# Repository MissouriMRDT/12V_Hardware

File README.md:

# 12V_Hardware
12V Distribution Board

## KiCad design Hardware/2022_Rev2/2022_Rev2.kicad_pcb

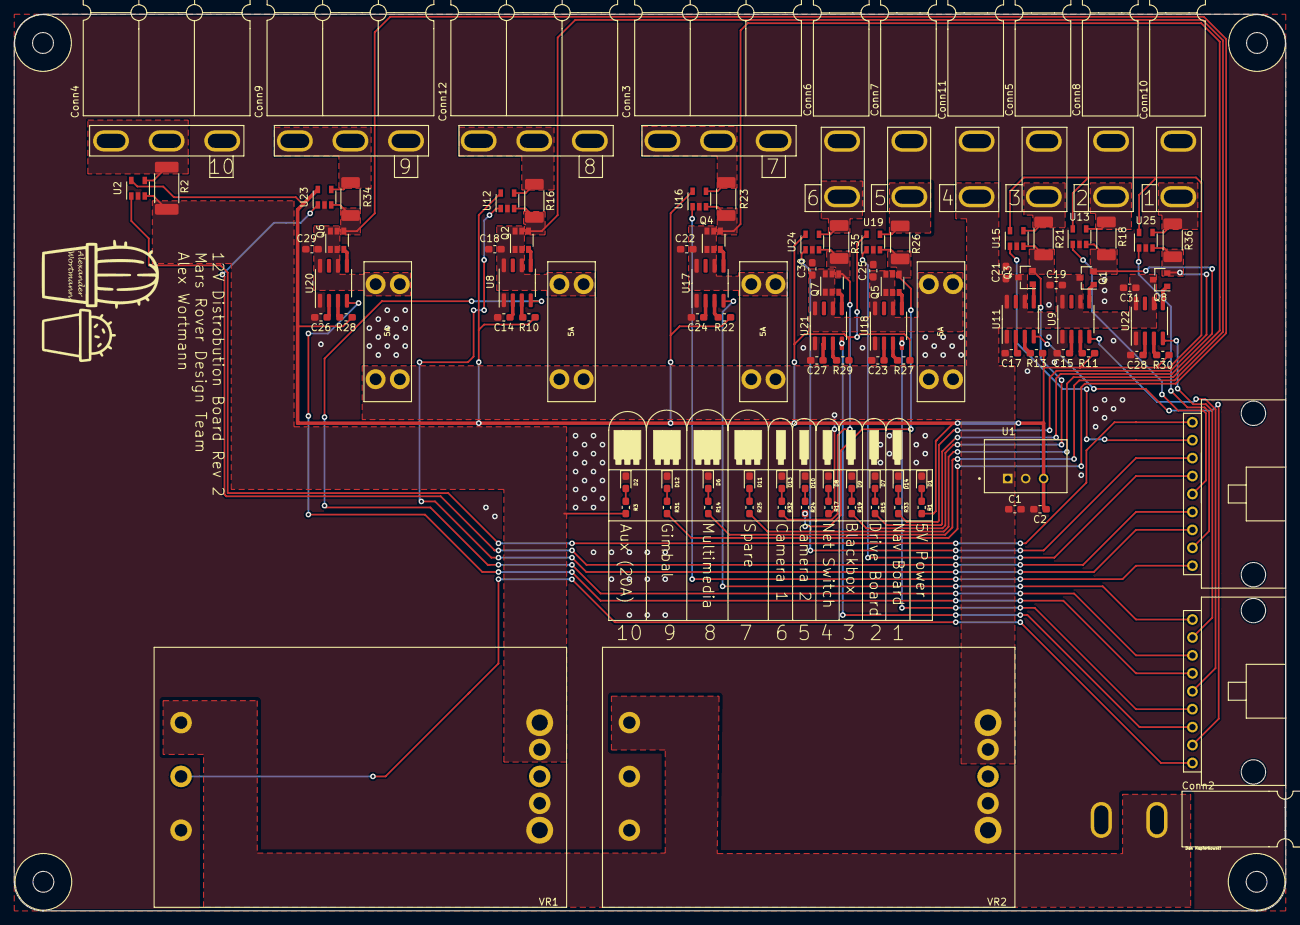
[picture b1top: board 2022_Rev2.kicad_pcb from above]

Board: 2 copper layers, 180.1 x 127.0 mm, 102 parts (0 on the bottom side), 79 nets.

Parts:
C1, C18, C19, C21, C22, C25, C29, C30, C31: 10uF; C_0603_1608Metric_Pad1.05x0.95mm_HandSolder
C2: 22uF; C_0603_1608Metric_Pad1.05x0.95mm_HandSolder
C14, C15, C17, C23, C24, C26, C27, C28: 0.1uF; C_0603_1608Metric_Pad1.05x0.95mm_HandSolder
Conn1, Conn13: Molex_SL_09; MOLEX_SL_09_Horizontal
Conn2: Pack; Square_Anderson_2_H_Stacked
Conn3: Spare; Square_Anderson_3_H_Side_By_Side
Conn4: Aux; Square_Anderson_3_H_Side_By_Side
Conn5: BBB; Square_Anderson_2_H_Stacked_PV
Conn6: Cam1; Square_Anderson_2_H_Stacked_PV
Conn7: Cam2; Square_Anderson_2_H_Stacked_PV
Conn8: Drive; Square_Anderson_2_H_Stacked_PV
Conn9: Gimbal; Square_Anderson_3_H_Side_By_Side
Conn10: Nav; Square_Anderson_2_H_Stacked_PV
Conn11: Network Switch; Square_Anderson_2_H_Stacked_PV
Conn12: Multimedia; Square_Anderson_3_H_Side_By_Side
D1, D2, D6, D7, D8, D9, D10, D11, D12, D13, D14: LED; D_0603_1608Metric_Pad1.05x0.95mm_HandSolder
F1, F6, F8, F9: 5A; ATC_Fuse_Block
Q1, Q3, Q8: IRLML2803TRPBF; SOT-23
Q2, Q4, Q5, Q6, Q7: FDC855N; SuperSOT-6
R1: 330; R_0603_1608Metric_Pad1.05x0.95mm_HandSolder
R2: 0.0015; R_2512_6332Metric_Pad1.52x3.35mm_HandSolder
R3, R14, R15, R17, R19, R24, R25, R31, R32, R33: 1k; R_0603_1608Metric_Pad1.05x0.95mm_HandSolder
R10, R11, R13, R22, R27, R28, R29, R30: 5.1k; R_0603_1608Metric_Pad1.05x0.95mm_HandSolder
R16, R18, R21, R23, R26, R34, R35, R36: 0.003; R_2010_5025Metric_Pad1.52x2.65mm_HandSolder
U1: TSR1-2433; TSR_1-2433
U2, U12, U13, U15, U16, U19, U23, U24, U25: INA281; SOT-23-5
U8, U9, U11, U17, U18, U20, U21, U22: LT1910; SOIC-8_3.9x4.9mm_P1.27mm
VR1, VR2: Q36SR12020NRFA

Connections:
+5V: C2.1, R1.2, R10.1, R11.1, R13.1, R22.1, R27.1, R28.1, R29.1, R30.1, U1.3, U2.5, U12.5, U13.5, U15.5, U16.5, U19.5, U23.5, U24.5, U25.5
+12VA: C1.1, C19.1, C21.1, C31.1, Conn11.2, F1.1, F6.1, F8.1, F9.1, Q1.3, Q3.3, Q8.3, R17.2, U1.1, U9.6, U9.8, U11.6, U11.8, U22.6, U22.8, VR2.7, VR2.8
+36V: Conn2.4, VR1.1, VR2.1
/12V/Anderson_BBB: Conn5.2, R21.2, U15.4
/12V/Anderson_Cam1: Conn6.2, R35.2, U24.4
/12V/Anderson_Cam2: Conn7.2, R26.2, U19.4
/12V/Anderson_Drive: Conn8.2, R18.2, U13.4
/12V/Anderson_GimAct: Conn9.2, Conn9.3, R34.2, U23.4
/12V/Anderson_MultiAct: Conn12.2, Conn12.3, R16.2, U12.4
/12V/Anderson_Nav: Conn10.2, R36.2, U25.4
/12V/Anderson_Spare: Conn3.2, Conn3.3, R23.2, U16.4
Current_Sense_Aux: Conn1.1, U2.1
Current_Sense_BBB: Conn1.2, U15.1
Current_Sense_Cam1: Conn1.3, U24.1
Current_Sense_Cam2: Conn1.4, U19.1
Current_Sense_Drive: Conn1.5, U13.1
Current_Sense_Gim: Conn1.6, U23.1
Current_Sense_Multi: Conn1.7, U12.1
Current_Sense_Nav: Conn1.8, U25.1
Current_Sense_Spare: Conn1.9, U16.1
Driver_Aux: Conn13.9, VR1.2
Driver_BBB: Conn13.8, U11.4
Driver_Cam1: Conn13.7, U21.4
Driver_Cam2: Conn13.6, U18.4
Driver_Drive: Conn13.5, U9.4
Driver_Gim: Conn13.4, U20.4
Driver_Multi: Conn13.3, U8.4
Driver_Nav: Conn13.2, U22.4
Driver_Spare: Conn13.1, U17.4
GND: C1.2, C2.2, C14.2, C15.2, C17.2, C18.2, C19.2, C21.2, C22.2, C23.2, C24.2, C25.2, C26.2, C27.2, C28.2, C29.2, C30.2, C31.2, Conn2.1, Conn3.1, Conn4.1, Conn5.1, Conn6.1, Conn7.1, Conn8.1, Conn9.1, Conn10.1, Conn11.1, Conn12.1, D1.1, D2.1, D6.1, D7.1, D8.1, D9.1, D10.1, D11.1, D12.1, D13.1, D14.1, U1.2, U2.2, U8.1, U9.1, U11.1, U12.2, U13.2, U15.2, U16.2, U17.1, U18.1, U19.2, U20.1, U21.1, U22.1, U23.2, U24.2, U25.2, VR1.3, VR1.4, VR1.5, VR2.2, VR2.3, VR2.4, VR2.5
unnamed: C14.1, U8.2
unnamed: C15.1, U9.2
unnamed: C17.1, U11.2
unnamed: C18.1, F6.2, Q2.1, Q2.2, Q2.5, Q2.6, U8.6, U8.8
unnamed: C22.1, F1.2, Q4.1, Q4.2, Q4.5, Q4.6, U17.6, U17.8
unnamed: C23.1, U18.2
unnamed: C24.1, U17.2
unnamed: C25.1, C30.1, F8.2, Q5.1, Q5.2, Q5.5, Q5.6, Q7.1, Q7.2, Q7.5, Q7.6, U18.6, U18.8, U21.6, U21.8
unnamed: C26.1, U20.2
unnamed: C27.1, U21.2
unnamed: C28.1, U22.2
unnamed: C29.1, F9.2, Q6.1, Q6.2, Q6.5, Q6.6, U20.6, U20.8
unnamed: Conn4.2, Conn4.3, R2.2, U2.4
unnamed: D1.2, R1.1
unnamed: D2.2, R3.1
unnamed: D6.2, R14.1
unnamed: D7.2, R15.1
unnamed: D8.2, R17.1
unnamed: D9.2, R19.1
unnamed: D10.2, R24.1
unnamed: D11.2, R25.1
unnamed: D12.2, R31.1
unnamed: D13.2, R32.1
unnamed: D14.2, R33.1
unnamed: Q1.1, U9.5
unnamed: Q1.2, R15.2, R18.1, U13.3
unnamed: Q2.3, U8.5
unnamed: Q2.4, R14.2, R16.1, U12.3
unnamed: Q3.1, U11.5
unnamed: Q3.2, R19.2, R21.1, U15.3
unnamed: Q4.3, U17.5
unnamed: Q4.4, R23.1, R25.2, U16.3
unnamed: Q5.3, U18.5
unnamed: Q5.4, R24.2, R26.1, U19.3
unnamed: Q6.3, U20.5
unnamed: Q6.4, R31.2, R34.1, U23.3
unnamed: Q7.3, U21.5
unnamed: Q7.4, R32.2, R35.1, U24.3
unnamed: Q8.1, U22.5
unnamed: Q8.2, R33.2, R36.1, U25.3
unnamed: R2.1, R3.2, U2.3, VR1.7, VR1.8
unnamed: R10.2, U8.3
unnamed: R11.2, U9.3
unnamed: R13.2, U11.3
unnamed: R22.2, U17.3
unnamed: R27.2, U18.3
unnamed: R28.2, U20.3
unnamed: R29.2, U21.3
unnamed: R30.2, U22.3

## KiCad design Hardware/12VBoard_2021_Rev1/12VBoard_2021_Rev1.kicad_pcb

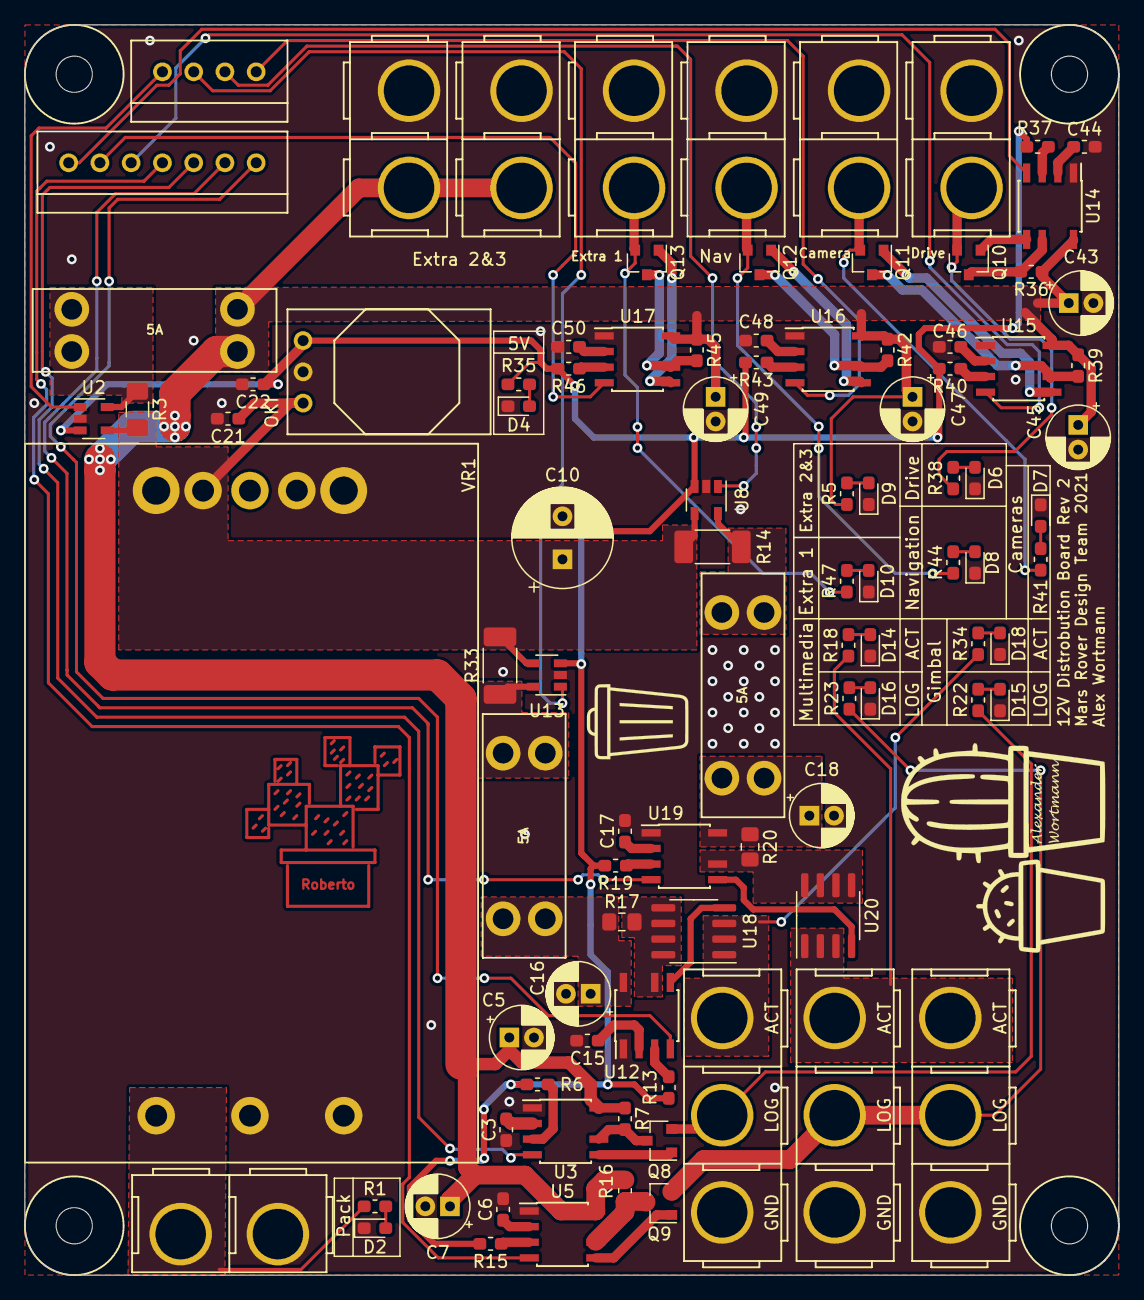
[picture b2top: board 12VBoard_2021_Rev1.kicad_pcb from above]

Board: 2 copper layers, 88.9 x 101.6 mm, 96 parts (0 on the bottom side), 72 nets.

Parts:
C3, C6, C15, C17, C44, C46, C48, C50: 0.1uF; C_0603_1608Metric_Pad1.05x0.95mm_HandSolder
C5, C7, C16, C18, C43, C45, C47, C49: 10uF; CP_Radial_D5.0mm_P2.00mm
C10: 330uF; CP_Radial_D8.0mm_P3.50mm
C21, C22: 10uF; C_0603_1608Metric_Pad1.05x0.95mm_HandSolder
Camera: Camera; Anderson_2_Vertical_Sidy_by_Side
Conn1: Molex_SL_10; MOLEX_SL_07_Vertical
Conn2: Molex_SL_05; MOLEX_SL_04_Vertical
Conn9: Gimbal; Anderson_3_Vertical_Side_by_Side
Conn11: Multimedia; Anderson_3_Vertical_Side_by_Side
Conn12: Extra; Anderson_3_Vertical_Side_by_Side
D2, D4, D6, D7, D8, D9, D10, D14, D15, D16, D18: LED; D_0603_1608Metric_Pad1.05x0.95mm_HandSolder
Drive: Drive; Anderson_2_Vertical_Sidy_by_Side
Extra 1: ExtraL1; Anderson_2_Vertical_Sidy_by_Side
Extra 2&3: ExtraL2; Anderson_2_Vertical_Sidy_by_Side
Extra 2&3#2: ExtraL3; Anderson_2_Vertical_Sidy_by_Side
F1, F2, F3: 5A; ATC_Fuse_Block
Nav: NavBoard; Anderson_2_Vertical_Sidy_by_Side
Pack: PackVoltage; Anderson_2_Vertical_Sidy_by_Side
Q8, Q9, Q10, Q11, Q12, Q13: IRLML2060; SOT-23
R1: 3.3k; R_0603_1608Metric_Pad1.05x0.95mm_HandSolder
R3: 20m; R_1206_3216Metric_Pad1.42x1.75mm_HandSolder
R5, R18, R22, R23, R34, R38, R41, R44, R47: 1.2k; R_0603_1608Metric_Pad1.05x0.95mm_HandSolder
R6, R13, R15, R19, R37, R40, R43, R46: 5.1K; R_0603_1608Metric_Pad1.05x0.95mm_HandSolder
R7, R16, R36, R39, R42, R45: 0.01; R_0603_1608Metric_Pad1.05x0.95mm_HandSolder
R14, R33: 20m; R_2010_5025Metric_Pad1.52x2.65mm_HandSolder
R17, R20: 0.01; R_0805_2012Metric_Pad1.15x1.40mm_HandSolder
R35: 510; R_0603_1608Metric_Pad1.05x0.95mm_HandSolder
U2, U8, U13: INA198; SOT-23-5
U3, U5, U12, U14, U15, U16, U17, U19: LT1910; SOIC-8-N7_3.9x4.9mm_P1.27mm
U9: OKI; OKI_Horizontal
U18, U20: FDS66900AS; SOIC-8_3.9x4.9mm_P1.27mm
VR1: Q36SR12020NRFA

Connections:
+5V: C22.1, R6.2, R13.2, R15.2, R19.2, R35.2, R37.2, R40.2, R43.2, R46.2, U2.3, U8.3, U9.3, U13.3
/High Current Outputs/12VActuation: C10.1, C21.1, R3.2, R14.2, R33.2, U2.4, U8.4, U9.1, U13.4, VR1.7, VR1.8
/High Current Outputs/12VLogic: C5.1, C7.1, C43.1, C45.1, C47.1, C49.1, Extra 2&3.2, Extra 2&3#2.2, F2.2, R5.1, R7.1, R16.1, R36.1, R39.1, R42.1, R45.1, U3.8, U5.8, U14.8, U15.8, U16.8, U17.8
/High Current Outputs/Gimbal/12V5AGimbal: Conn9.3, R34.1, U18.1, U18.2, U18.3
/High Current Outputs/Gimbal/12V5AON: C16.1, F3.1, R17.1, U12.8
/High Current Outputs/Gimbal/12VLogicGimbal: Conn9.2, Q8.2, R22.1
/High Current Outputs/GimbalCTL_Act: Conn1.1, U12.4
/High Current Outputs/GimbalCTL_Log: Conn1.3, U3.4
/High Current Outputs/GimbalSense: Conn2.3, U13.1
/High Current Outputs/MultiMediaCTL_Log: Conn1.4, U5.4
/High Current Outputs/Multimedia/Extra/12V5AMultiMedia: Conn11.3, Conn12.3, R18.1, U20.1, U20.2, U20.3
/High Current Outputs/Multimedia/Extra/12V5AON: C18.1, F1.1, R20.1, U19.8
/High Current Outputs/Multimedia/Extra/12VLogicMultiMedia: Conn11.2, Conn12.2, Q9.2, R23.1
/High Current Outputs/MultimediaCTL_Act: Conn1.2, U19.4
/High Current Outputs/MultimediaSense: Conn2.2, U8.1
/High Current Outputs/PackVoltage: Pack.2, R1.1, VR1.1
/Low Current Outputs/CameraCTL: Conn1.5, U15.4
/Low Current Outputs/CurrentSense: Conn2.4, U2.1
/Low Current Outputs/DriveCTL: Conn1.7, U14.4
/Low Current Outputs/ExtraCTL: Conn1.6, U17.4
/Tiva In/Outputs/NavBoardCTL: Conn2.1, U16.4
GND: C3.2, C5.2, C6.2, C7.2, C10.2, C15.2, C16.2, C17.2, C18.2, C21.2, C22.2, C43.2, C44.2, C45.2, C46.2, C47.2, C48.2, C49.2, C50.2, Camera.1, Conn9.1, Conn11.1, Conn12.1, D2.1, D4.1, D6.1, D7.1, D8.1, D9.1, D10.1, D14.1, D15.1, D16.1, D18.1, Drive.1, Extra 1.1, Extra 2&3.1, Extra 2&3#2.1, Nav.1, Pack.1, U2.2, U3.1, U5.1, U8.2, U9.2, U12.1, U13.2, U14.1, U15.1, U16.1, U17.1, U19.1, VR1.2, VR1.3, VR1.4, VR1.5
unnamed: C3.1, U3.2
unnamed: C6.1, U5.2
unnamed: C15.1, U12.2
unnamed: C17.1, U19.2
unnamed: C44.1, U14.2
unnamed: C46.1, U15.2
unnamed: C48.1, U16.2
unnamed: C50.1, U17.2
unnamed: Camera.2, Q11.2, R41.1
unnamed: Nav.2, Q12.2, R44.1
unnamed: Extra 1.2, Q13.2, R47.1
unnamed: Drive.2, Q10.2, R38.1
unnamed: D2.2, R1.2
unnamed: D4.2, R35.1
unnamed: D6.2, R38.2
unnamed: D7.2, R41.2
unnamed: D8.2, R44.2
unnamed: D9.2, R5.2
unnamed: D10.2, R47.2
unnamed: D14.2, R18.2
unnamed: D15.2, R22.2
unnamed: D16.2, R23.2
unnamed: D18.2, R34.2
unnamed: F1.2, R14.1, U8.5
unnamed: F2.1, R3.1, U2.5
unnamed: F3.2, R33.1, U13.5
unnamed: Q8.1, U3.5
unnamed: Q8.3, R7.2, U3.6
unnamed: Q9.1, U5.5
unnamed: Q9.3, R16.2, U5.6
unnamed: Q10.1, U14.5
unnamed: Q10.3, R36.2, U14.6
unnamed: Q11.1, U15.5
unnamed: Q11.3, R39.2, U15.6
unnamed: Q12.1, U16.5
unnamed: Q12.3, R42.2, U16.6
unnamed: Q13.1, U17.5
unnamed: Q13.3, R45.2, U17.6
unnamed: R6.1, U3.3
unnamed: R13.1, U12.3
unnamed: R15.1, U5.3
unnamed: R17.2, U12.6, U18.5, U18.6, U18.7, U18.8
unnamed: R19.1, U19.3
unnamed: R20.2, U19.6, U20.5, U20.6, U20.7, U20.8
unnamed: R37.1, U14.3
unnamed: R40.1, U15.3
unnamed: R43.1, U16.3
unnamed: R46.1, U17.3
unnamed: U12.5, U18.4
unnamed: U19.5, U20.4

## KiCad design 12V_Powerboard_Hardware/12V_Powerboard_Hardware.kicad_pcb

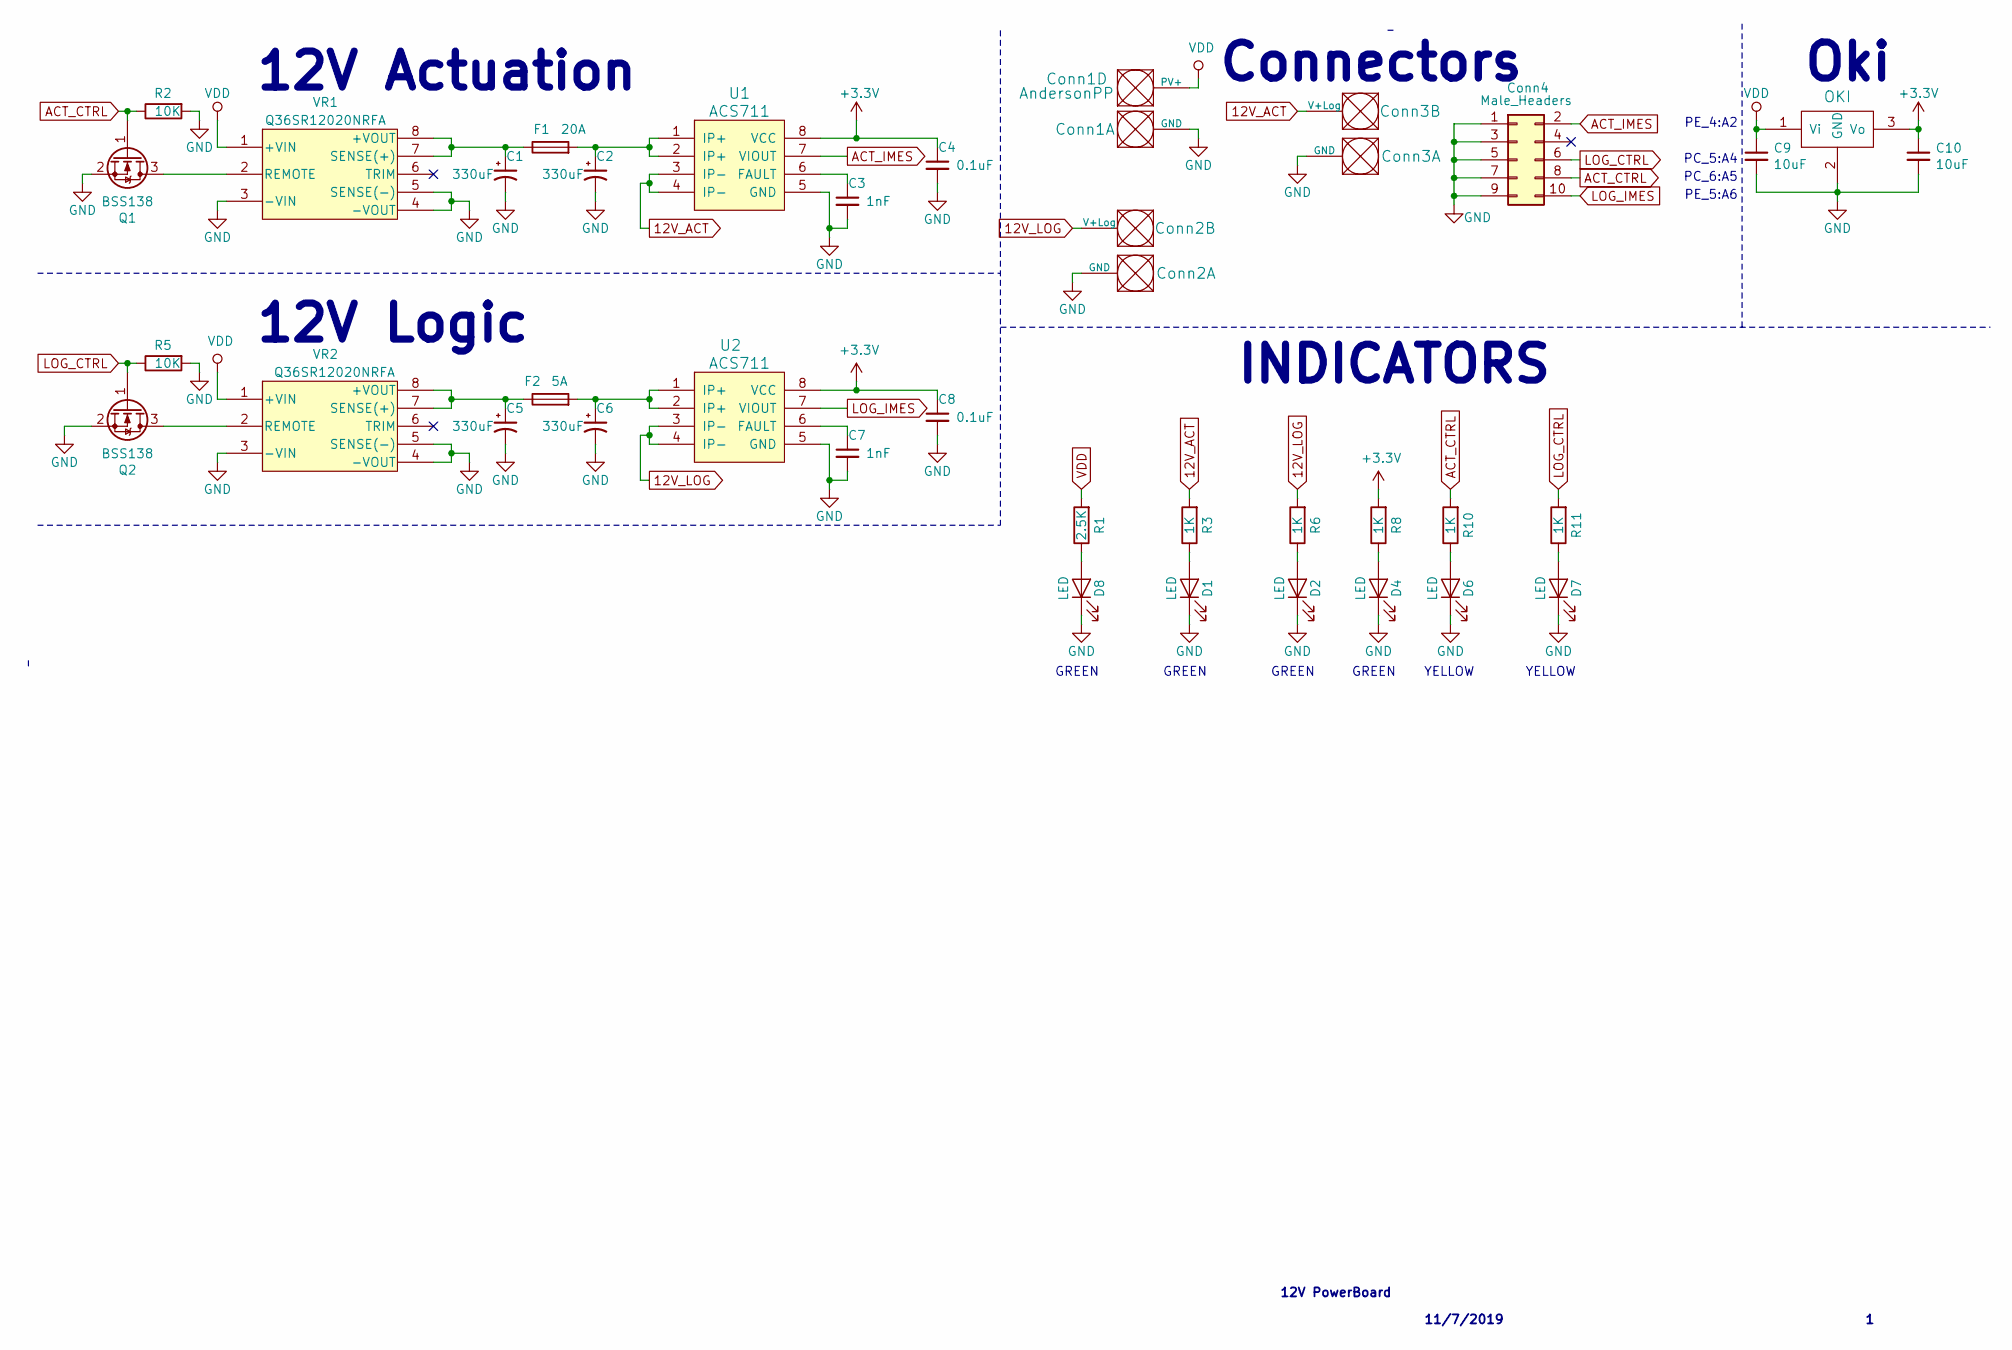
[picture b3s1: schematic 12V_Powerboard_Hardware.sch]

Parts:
C1, C2, C5, C6: 330uF; CP_Radial_D8.0mm_P3.50mm
C3, C7: 1nF; C_0603_1608Metric_Pad1.05x0.95mm_HandSolder
C4, C8: 0.1uF; C_0603_1608Metric_Pad1.05x0.95mm_HandSolder
C9, C10: 10uF; C_0603_1608Metric_Pad1.05x0.95mm_HandSolder
Conn1: AndersonPP; Anderson_2_Horizontal_Stacked
Conn2, Conn3: AndersonPP; Anderson_2_Vertical_Sidy_by_Side
Conn4: Male_Headers; JTAG_ARM_Connector_10_Pin
D1, D2, D4, D6, D7, D8: LED; LED_0603_1608Metric_Pad1.05x0.95mm_HandSolder
F1: 20A; ATC_Fuse_Block
F2: 5A; ATC_Fuse_Block
Q1, Q2: BSS138; SOT-323_SC-70_Handsoldering
R1: 2.5K; R_0603_1608Metric_Pad1.05x0.95mm_HandSolder
R2, R5: 10K; R_0603_1608Metric_Pad1.05x0.95mm_HandSolder
R3, R6, R8, R10, R11: 1K; R_0603_1608Metric_Pad1.05x0.95mm_HandSolder
U1, U2: ACS711; SOIC-8_3.9x4.9mm_P1.27mm
U5: OKI; OKI_Horizontal
VR1, VR2: Q36SR12020NRFA

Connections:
12V_ACT: Conn3.2 (V+Log), R3.2, U1.3 (IP-), U1.4 (IP-)
12V_LOG: Conn2.2 (V+Log), R6.2, U2.3 (IP-), U2.4 (IP-)
+3V3: C4.1, C8.1, C10.1, R8.2, U1.8 (VCC), U2.8 (VCC), U5.3 (Vo)
ACT_CTRL: Conn4.8, Q1.1 (G), R2.1, R10.2
ACT_IMES: Conn4.2, U1.7 (VIOUT)
GND: C1.2, C2.2, C3.2, C4.2, C5.2, C6.2, C7.2, C8.2, C9.2, C10.2, Conn1.1 (GND), Conn2.1 (GND), Conn3.1 (GND), Conn4.1, Conn4.3, Conn4.5, Conn4.7, Conn4.9, D1.1 (K), D2.1 (K), D4.1 (K), D6.1 (K), D7.1 (K), D8.1 (K), Q1.2 (S), Q2.2 (S), R2.2, R5.2, U1.5 (GND), U2.5 (GND), U5.2 (GND), VR1.3 (-VIN), VR1.4 (-VOUT), VR1.5 (SENSE(-)), VR2.3 (-VIN), VR2.4 (-VOUT), VR2.5 (SENSE(-))
LOG_CTRL: Conn4.6, Q2.1 (G), R5.1, R11.2
LOG_IMES: Conn4.10, U2.7 (VIOUT)
unnamed: C1.1, F1.1, VR1.7 (SENSE(+)), VR1.8 (+VOUT)
unnamed: C2.1, F1.2, U1.1 (IP+), U1.2 (IP+)
unnamed: C3.1, U1.6 (FAULT)
unnamed: C5.1, F2.1, VR2.7 (SENSE(+)), VR2.8 (+VOUT)
unnamed: C6.1, F2.2, U2.1 (IP+), U2.2 (IP+)
unnamed: C7.1, U2.6 (FAULT)
unnamed: D1.2 (A), R3.1
unnamed: D2.2 (A), R6.1
unnamed: D4.2 (A), R8.1
unnamed: D6.2 (A), R10.1
unnamed: D7.2 (A), R11.1
unnamed: D8.2 (A), R1.1
unnamed: Q1.3 (D), VR1.2 (REMOTE)
unnamed: Q2.3 (D), VR2.2 (REMOTE)
VDD: C9.1, Conn1.4 (PV+), R1.2, U5.1 (Vi), VR1.1 (+VIN), VR2.1 (+VIN)

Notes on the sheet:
12V Logic
12V PowerBoard
11/7/2019
12V Actuation
Oki
PE_4:A2
PE_5:A6
PC_6:A5
PC_5:A4
Connectors
GREEN
YELLOW
INDICATORS

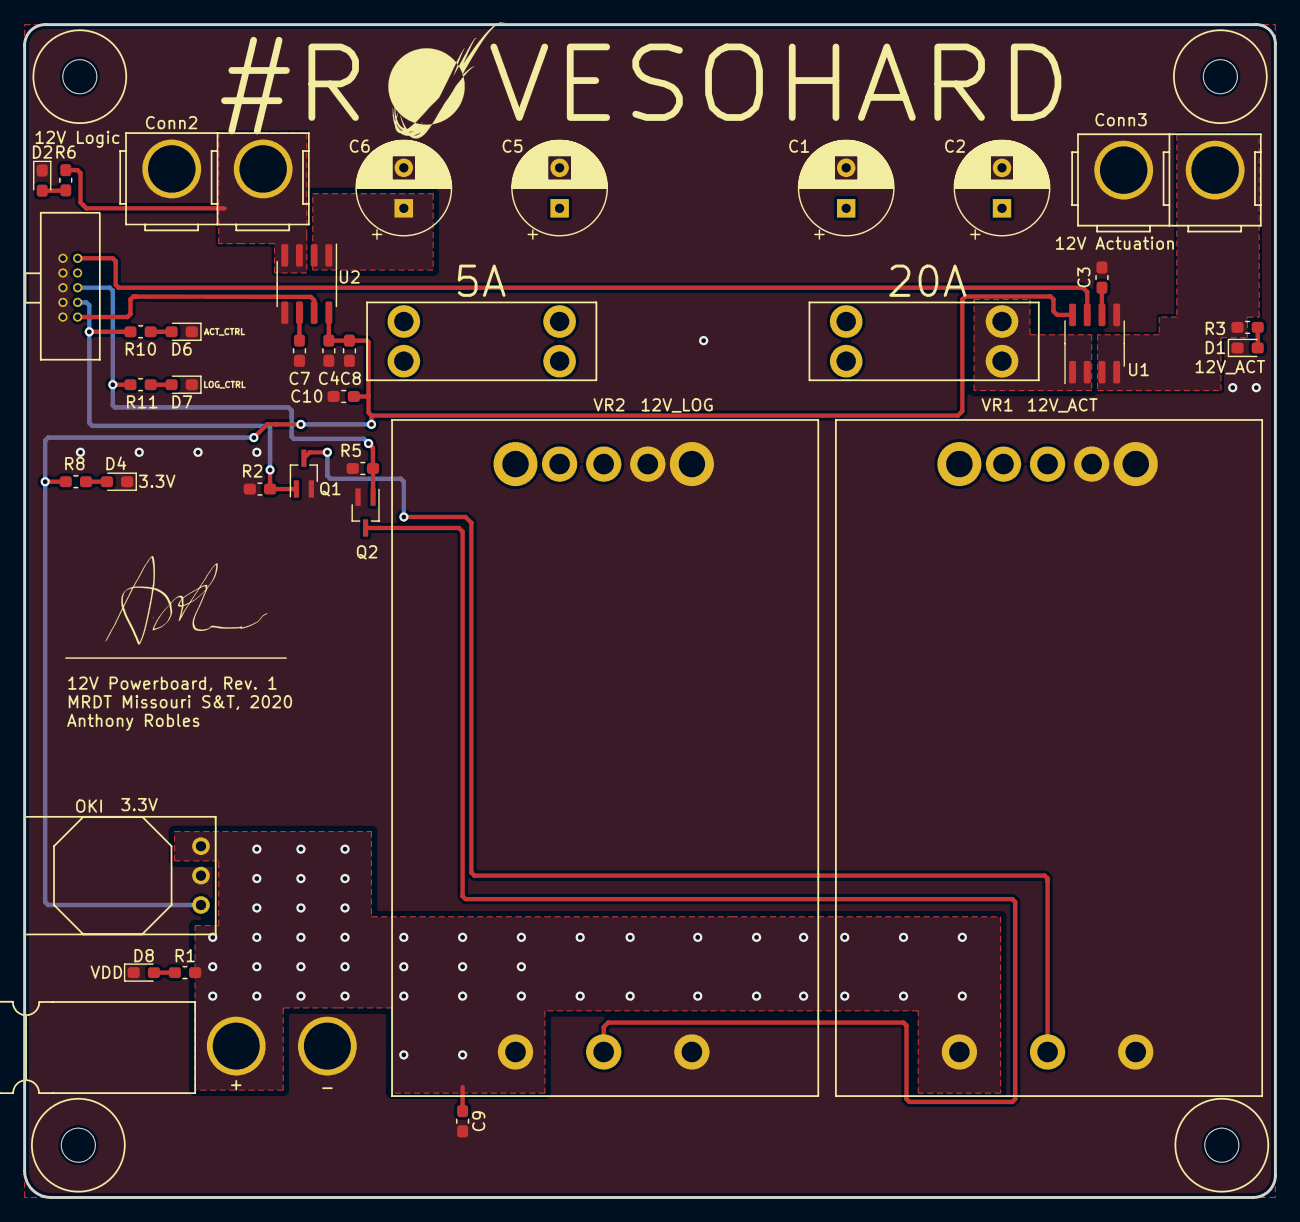
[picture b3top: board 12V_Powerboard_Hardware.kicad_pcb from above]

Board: 2 copper layers, 108.1 x 101.3 mm, 37 parts (0 on the bottom side), 23 nets.

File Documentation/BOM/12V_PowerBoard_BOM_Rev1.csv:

Id,Designator,Package,Quantity,Designation,Item Name,Part Number,Vendor,Cost Per Item,Cost,URL,Comments,,,
1,Conn4,PinHeader_2x05_P1.27mm_Vertical,1,Male_Headers,CONN HEADER VERT 10POS 1.27MM ,1175-1627-ND ,Digikey,$0.58 ,$0.58 ,https://www.digikey.com/product-detail/en/cnc-tech/3220-10-0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,,,,Total Cost
2,"VR2,VR1",Q36SR12020NRFA,2,Q36SR12020NRFA,DC DC CONVERTER 12V 240W,941-1762-ND,Digikey,$63.25 ,$126.50 ,https://www.digikey.com/products/en?keywords=941-1762-ND,,,,$84.35 
3,"Q2,Q1",SOT-323_SC-70_Handsoldering,2,BSS138,"MOSFET Transistor, N Channel, 220 mA, 50 V, 0.7 ohm, 10 V, 1.3 V",58K8769,Newark,$0.30 ,$0.60 ,https://www.newark.com/on-semiconductor/bss138/n-channel-mos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,,,,
4,"C6,C5,C2,C1",CP_Radial_D8.0mm_P3.50mm,4,330uF," Polymer Aluminium Electrolytic Capacitor, 330 µF, 25 V, Radial Leaded",33AC4449,Newark,$1.56 ,$6.24 ,https://www.newark.com/nichicon/rnu1e331mdnasq/cap-alu-polym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,,,,
5,U5,OKI_Horizontal,1,OKI,OKI-78SR-3.3,58T9850,Newark,$4.57 ,$4.57 ,https://www.newark.com/murata-power-solutions/oki-78sr-3-3-1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,,,,
6,"C8,C4",C_0603_1608Metric_Pad1.05x0.95mm_HandSolder,2,0.1uF,"SMD Multilayer Ceramic Capacitor, 0.1 µF, 16 V, 0603 [1608 Metric], ± 10%, X7R, CL Series",82AC9325,Newark,$0.09 ,$0.18 ,https://www.newark.com/samsung-electro-mechanics/cl10b104ko8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,,,,
7,"C7,C3",C_0603_1608Metric_Pad1.05x0.95mm_HandSolder,2,1nF,SMD Multilayer Ceramic Capacitor,82AC9201,Newark,$0.09 ,$0.18 ,https://www.newark.com/samsung-electro-mechanics/cl05b102kb5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,,,,
8,"D3,D2,D1",LED_0603_1608Metric_Pad1.05x0.95mm_HandSolder,3,LED,"LED, QuasarBrite, Green, SMD, 0603",75K1440,Newark,$0.24 ,$0.73 ,"https://www.newark.com/lumex/sml-lx0603gw-tr/led-green-0-8mm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,%20QuasarBrite,%20Green,%20SMD,%200603,%2020%20mA,%202%20V",,,,
9,"U2,U1",SOIC-8_3.9x4.9mm_P1.27mm,2,ACS711,"Current Sensor, Overcurrent Fault, 4 mA",71T9736,Newark,$3.04 ,$6.08 ,https://www.newark.com/allegro-microsystems/acs711klctr-12ab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,,,,
10,"R6,R3",R_0603_1608Metric_Pad1.05x0.95mm_HandSolder,2,1K," RES, 1K",59AC6943,Newark,$0.10 ,$0.20 ,https://www.newark.com/rohm/esr03ezpj102/res-1k-5-0603-thick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,,,,
11,"R5,R2",R_0603_1608Metric_Pad1.05x0.95mm_HandSolder,2,10K,"RES, 10K",59AC6935,Newark,$0.12 ,$0.24 ,https://www.newark.com/rohm/esr03ezpf1002/res-10k-1-0603-thi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,,,,
12,"F2,F1",ATC_Fuse_Block,2,"5A,20A","Fuseholder, Automotive, 500V, 20A",22M2712,Newark,$1.03 ,$2.06 ,https://www.newark.com/keystone/3557-2/fuse-holder-auto-blad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,,,,
13,F1,20A_Fuse,1,20A,"Automotive Fuse, 32 V, 20 A",24W7935,Newark,$0.14 ,$0.14 ,https://www.newark.com/littelfuse/0287020-pxcn/automotive-fu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,,,,
14,F2,5A_Fuse,1,5A,"Automotive Fuse, 32 V, 5 A",24W7932,Newark,$0.27 ,$0.27 ,https://www.newark.com/littelfuse/0287005-pxcn/automotive-fu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,,,,
15,"Conn5,Conn1",Anderson_2_Horizontal_Stacked,2,AndersonPP,PCB Horizontal Top Contact,1337G1 ,Powerwerx,$0.56 ,$1.12 ,https://powerwerx.com/anderson-1337g1-printed-circuit-board-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,,,,
16,"Conn5,Conn1",Anderson_2_Horizontal_Stacked,2,AndersonPP,PCB Horizontal Bottom Contact,1336G1,Powerwerx,$0.55 ,$1.10 ,https://powerwerx.com/anderson-1336g1-printed-circuit-board-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,,,,
17,"Conn3,Conn2",Anderson_2_Vertical_Sidy_by_Side,2,AndersonPP,PCB Vertical Contact,1335G1 ,Powerwerx,$0.59 ,$1.18 ,https://powerwerx.com/anderson-1335g1-printed-circuit-board-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,,,,
18,Connector Housing,Anderson Housing,4,AndersonPP,Black Housing,1327G6,Powerwerx,$0.37 ,$1.48 ,https://powerwerx.com/anderson-powerpole-colored-housings,,,,
19,Connector Housing,Anderson Housing,2,AndersonPP,Red Housing,1327,Powerwerx,$0.37 ,$0.74 ,https://powerwerx.com/anderson-powerpole-colored-housings,,,,
20,Connector Housing,Anderson Housing,2,AndersonPP,Blue Housing,1327G8,Powerwerx,$0.39 ,$0.78 ,https://powerwerx.com/anderson-powerpole-colored-housings,,,,

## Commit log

2020-09-11 Merged 2020 with master
2020-09-18 Project and folders created
2020-09-30 Create hierarchical sheets
2020-10-04 BD9811MUV symbol made along with most supporting circuits
2020-10-04 fixed things
    project folders, IC symbol size, library
2020-10-04 Finished layingout componets needed for buck converter
2020-10-07 Created Buck Circuts
    added boxes that Dan hates
2020-10-10 High current
    Hiearchial setup of high current. started working on high current setup with anderson.
2020-10-10 YELLED AT DAN WITHOUT HIM HERE
2020-10-13 current sense
    started current sense circuit on hig current. added fuse and LED signal. started tiva wiring.
2020-10-14 current sense
    finished adding current sensing to high current side, also started thinking about tiva pin connector layout
2020-10-14 Ferite bead?
    MERGE?????
2020-10-14 SHOCKKY :D
    anthony mad
2020-10-15 finished low current
2020-10-15 High current
    Fisnished adding labes/tags
2020-10-17 Added Testpoints
2020-10-17 reviewed
    review
2020-10-21 Changed things
    Dans a quitter
2020-10-22 fixed High current for second review
    addes gimbal to high current. added teva digital write pin to gimbal fot CTL. changed ports from 15 to 10 amp
2020-10-26 Changed buck names
2020-10-26 Connector change
    added current sense to gimbal and changed tiva header to two molex connectors to allow for more pins
2020-10-27 fixed some stuffs
2020-11-01 LM5116
    Replaced DB ic with LM5116. Need to add values.
2020-11-05 Added Component Values.
    Added values to high side buck and
    footprints to components.
2020-11-05 changed current sensor
    chnaged the current sesor resistor to 50m
2020-11-06 Finished Footprint Assignment
    added footprint for switch and finished footprint assigning aslwell as changeing low current current sense resistor to 50 m ohms.
2020-11-10 Added Logic power circuits (High)
    Added three smaller bucks for high current logic power and seprated acuation and logic pp
2020-11-10 Layout Started
    Board dimensions
2020-11-10 kiCad was erroring out when it didnt need to
    also changed anderson to horizontal side by side.
2020-11-11 Worked on layout
    Low current bucks grouped with their componets
2020-11-11 Missing footprints issue found
    Library difference between computer caused footprints not to appear on the layout
2020-11-12 Fixed Resistor and Capasitor footprints
    found other issues
2020-11-12 Fixed Nets for andersons
2020-11-14 High side layout started with grouping components
2020-11-14 Components
    Added the correct mosfets for the extra and the high current bucks
2020-11-15 updated footprints
2020-11-15 Layout kinda finished
2020-11-15 Started Laying out bucks
2020-11-15 Placed all Logic Only Bucks
2020-11-15 reorginized traces
2020-11-15 Started High Current Tracing
    (Crash happened)
2020-11-16 packVoltage line not connected in schematic
    Sheet pins were used instead of hierarchical pins, which caused the line to not be continuous. Now it is connected
2020-11-16 Checked H pins
2020-11-16 fixed H pins x2
2020-11-16 mosfet Net issue: one resolved
    the footprint was not updating correctly and had incorrect nets
2020-11-16 Fixed all nets on Mosfets
2020-11-16 Finished layout of First high current buck
2020-11-16 First Buck Arranged
2020-11-16 Re arranged bucks for more space
2020-11-16 Lunch Break
    Routing thinzs
2020-11-16 Finished first full high side layout
2020-11-16 All Bucks finalized
2020-11-17 Traces
    finalized all traces
2020-11-17 Made Silkscreen Boxes
2020-11-17 Fixed Ground islands
2020-11-18 Aded oki and started change of high side logic setup
2020-11-18 Changes!
    Added the new correct connectors and redid all signal lines to the High Current side of the board. Also deleted all uncessacary components on the High current side that are no longer used.
2020-11-19 Added Mosfet cicuitry to turn on/off logic power for high current side
2020-11-28 Redesigned low current ports schematic
2020-11-28 Layed out logic power
2020-11-29 Added Inductor Footprint
2020-11-29 Started layout of bucks
2020-11-29 found Big inductors
2020-11-29 Added all logic circuits for high current
2020-11-29 Rearanged logic bick for high current
2020-11-29 Extended Board
2020-11-29 I changed stuff
2020-11-30 changed to big bucks
    changed to the bucks used in Master due to a realization in the inductor sizing for the LM5116. It would be much bigger than previous years.
2020-11-30 Started work on updated layout
2020-11-30 Layout for high current
2020-11-30 did planes for high current
2020-12-01 Routing of mosfet drivers and current sensors
2020-12-01 LED work, started on control signals
2020-12-01 fisnished board traces
    still a problem with 12VAcuation
2020-12-01 fixed 12VAcutation issue
2020-12-02 admin changes
    -current sensing on high current
    -fixed traces for current sensing
2020-12-02 Started work on BOM
2020-12-03 fixed spacing on BOM
2020-12-04 Added signature to board
2020-12-04 Discovered problems, will fix on next pushes
2020-12-04 Fixed problem
2020-12-05 Fixed ground plane issue
2020-12-14 BOM Work
2020-12-14 BOM almost done
    some things were not updated from newest layout and 330uF capacitor is not present in the BOM
2020-12-14 BOM completed
    Checklist: -BOM done
    To do: Gerbs
2020-12-14 Gerbs ?Sketch?
2021-01-05 BOM fixed
    some components were selected incorrectly and there is still a board error with one of the footprints being off a bit
2021-02-22 Started Rev 2
2021-02-22 edited traces
2021-02-23 updated Rev2
2021-02-23 Updated silkscreens
2021-02-25 Rev 2 redone
    in conclusion rev2=rev3 but its really rev12
2021-02-26 changed silk screens
2021-03-30 Reran some traces to improve visuals and ground
2021-04-02 gerbs
2022-02-20 Deleted old files and started on new 12V board
2022-02-23 Added Heirarchical Labels inside the 12V sheet
2022-02-26 Organized some stuff and added Teensy connections
2022-02-26 closed file
2022-02-26 Named the 12Volt Board
2022-03-09 Tiva implementation
2022-03-09 change switch circuit naming + added more switch circuits.
2022-03-10 back to the teensy :alien:
2022-03-10 12v switch circuits added
2022-03-10 teensy pins are done (I think)
2022-03-10 andersons done
2022-03-10 molex pins
2022-03-10 removed scilog/sciact
2022-03-10 molex pins pt.2
2022-03-10 assigning footprints pt.1
2022-03-10 Finished footprint signatures and started schematic
2022-03-11 fixed footprints
2022-03-11 Create fp-info-cache
2022-03-12 Lots of Changes
2022-03-12 Fixed schematic and fixed annotations
2022-03-12 Assigned footprints and finished changes on schem
2022-03-16 Fixed many issues
2022-03-17 ahhhhhh ladybug is angy
2022-03-18 Gerbs are done
    please review before you order this max
2022-03-18 made a comment about the current sensor
2022-03-18 changed board review complaints
    generated gerbs
2022-04-06 Generated step file
2022-04-27 Created BOM
2022-05-02 renamed bom
